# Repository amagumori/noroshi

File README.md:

# Noroshi
#### Portable LTE/Wifi Radio Terminal

Noroshi is a project that aims to explore the question:
**What capabilities enabled by the Internet are compelling, and...**
**How can we provide those capabilities in a way that is:**

+ More decentralized
+ More autonomous
+ More empowering for the individual?

The Internet of today is a vastly different place from the days of its infancy.  We've moved from a "many-servers" paradigm to a "many-clients" paradigm, as monolithic platforms have conquered the space.  The majority of Internet communication now exists in a TV-like paradigm, with a single-digit number of service providers.

These providers provide a variety of technological capabilities, each with unique social and cultural relevance, which overlap and can be broadly grouped into "live" and "static" groups, though the "liveness" is a spectrum.

### Live Capabilities
**Streaming** - Youtube, Twitch, IG Live, FB Live.
**Group Chat** - Discord, Slack, IRC (barely hanging on)
**Messaging** - Every platform

### Slow Capabilities
**Microblogging** - Twitter, IG, FB
**File Sharing** - Google Drive, Dropbox, OneDrive, etc
**Email** - Gmail, of course
**~~Blogging~~**  doesn't exist anymore
**~~Websites~~** don't exist anymore (in social or cultural relevance)

---

What would it look like to envision off-internet networking at a community or friend-group level?  And what capabilities could we provide while remaining free from the Internet or monolithic service providers?

The Internet provides a variety of capabilities, from realtime, streaming applications to static data.  We aim to attack this problem on both ends - one, the streaming, realtime, low-latency side of Internet functionality, using the NRF9160 to communicate over LTE; and the other, the slower, static side, using the ESP32 to enable peer-to-peer data exchange over Wifi.

### On the LTE side, a "radio" mode of using internet connectivity.  

+ Secure, frictionless, realtime push-to-talk communication, as with a VHF/UHF radio.

+ Broadcasting and receiving streaming audio, as with an FM radio.

Both of these applications are out of reach for the "regular citizen", especially within a city.  Ham radio does not enable encrypted communications, and is limited by regulation to a pure hobbyist pursuit.  Ham cannot be used for group-exclusive communications, and has a variety of limitations and frictions that prevent it from being a viable day-to-day communication tool.

On the other side, to set up a private VHF/UHF PTT capability within a city, a customer must lease radios from a vertically integrated provider, because only these will own repeater space on the local coverage points; you can get licensed, but a prohibitively expensive outlay is required to actually achieve full coverage in a metropolitan area.

These regulatory limitations prevent VHF/UHF from being used in an autonomous, secure, and self-sufficient manner.  Either you're a HAM, limited to communications-as-a-hobby - QSLs, etc; or you're a lessee of service from a provider.

This project aims to take a specific, compelling application of cell technology (low-latency audio streaming) and build a dedicated, stripped-down, and focused product for it, providing a more autonomous and open-source way to use IoT without relying on current monolithic tech ecosystems.

The goal of this project is to provide a different vision of communication over cell networks.  The value of this radio is in it being a dedicated object with a focused purpose and frictionless UX.  We aim for the main mode of interaction with the object to be physical, with the screen providing extremely concise information.  As far as possible from the interaction mode of a mobile app, we want this to be a physical device that fits well in the hand, has interactions recognizable by feel, and can be used without looking at the screen.

To illustrate this, mobile apps like Zello enable PTT functionality; but they also require buying into the entire cell phone ecosystem, from the hardware to the OS, and your communications go through an opaque signed binary to Zello's servers.  Cell phone apps have ever-present interaction friction at every level - multiple touch interactions to talk by default (unlocking the screen to hit the talk button, etc); coexisting with other apps on the phone, which can interfere with its operation or availability; difficulty of manipulating the phone in the hand; and so on.

Similarly, internet radio already exists; but there is no *dedicated* and simplified way to interact with it, and as such the technology is effectively dead.  Streaming video platforms such as Youtube or Twitch are now the dominant platform for audio streaming, because they provide lower barriers to entry and vastly better UX than Shoutcast or similar.  By providing a simple and frictionless way to broadcast and receive audio in realtime, we aim to empower individual users and rejuvenate a dying medium, with everyone being the owner, operator, and DJ of their own radio station, not through an app, but through a dedicated physical device.  Ultimately, I envision this as pushing a second age of radio, with individuals able to frictionlessly "speak" to an audience - every individual having space within the frequency spectrum, free of barriers to entry.

### Wifi / LoRa - Wifi for a peer-to-peer sneakernet, decoupled from the Internet.

The aim of the Wifi side of functionality is to provide a way to slowly and organically share static data among a local community without using the Internet - in other words, to provide a truly autonomous form of social networking.  

This aims at a similar area as existing platforms such as Mastodon that aim to provide decentralized alternatives to monolithic social networks. This project aims to provide a generic and open-ended framework for all types of information exchange - social applications like microblogging, as well as media and file sharing, forums, and wikis.  It also aims to provide a hardy and simple method for updating this shared state, that can be used not just with WiFi, but with other wireless connections - LoRa, etc.

## Design Methodology

We envision a community's "shared state" as a traditional filesystem, with each member possessing a directory.  At a global level, there are N numbers of dedicated *reserved filenames* that indicate the contextual meaning of the data.  a directory named "blog" will be viewed on the client side as that user's blog, similar to a twitter feed.  all files within that directory will be parsed as Markdown and displayed as blog entries in a time-sorted list based on the file's creation date.

### Connection

The public keys of "friends" in the community are indicated by the SSID broadcasted by the peer AP, and the shared secret is used as the WPA2 password.  With both devices in Station+SoftAP mode, operating in both modes simultaneously, we open a TCP socket connection.

### Syncing

After connecting to the peer, both clients send hashes of each "friend"'s directory, as well as timestamps of its last update.  both clients symmetrically use this info to determine the friends for which they own newer data, and the friends for which they own older data.

Another *reserved file* is the "friends" file.  This file exists within each person's directory at the top level, and describes permission groups (The ESP32 has a stripped-down libc, but runs on FreeRTOS, and has a very spare filesystem abstraction layer.)

We use **librsync**, specifically **rdiff**, to handle generating file signatures, deltas, and patching.  Signature files are generated AoT, not at connection time.

The friend directory trees are walked with **ftw**, permissions are checked, and the fds of new / updated signature files are pushed to a queue.  These signature files are compressed and sent; used to generate deltas; and deltas are compressed and sent, completing the sync process.

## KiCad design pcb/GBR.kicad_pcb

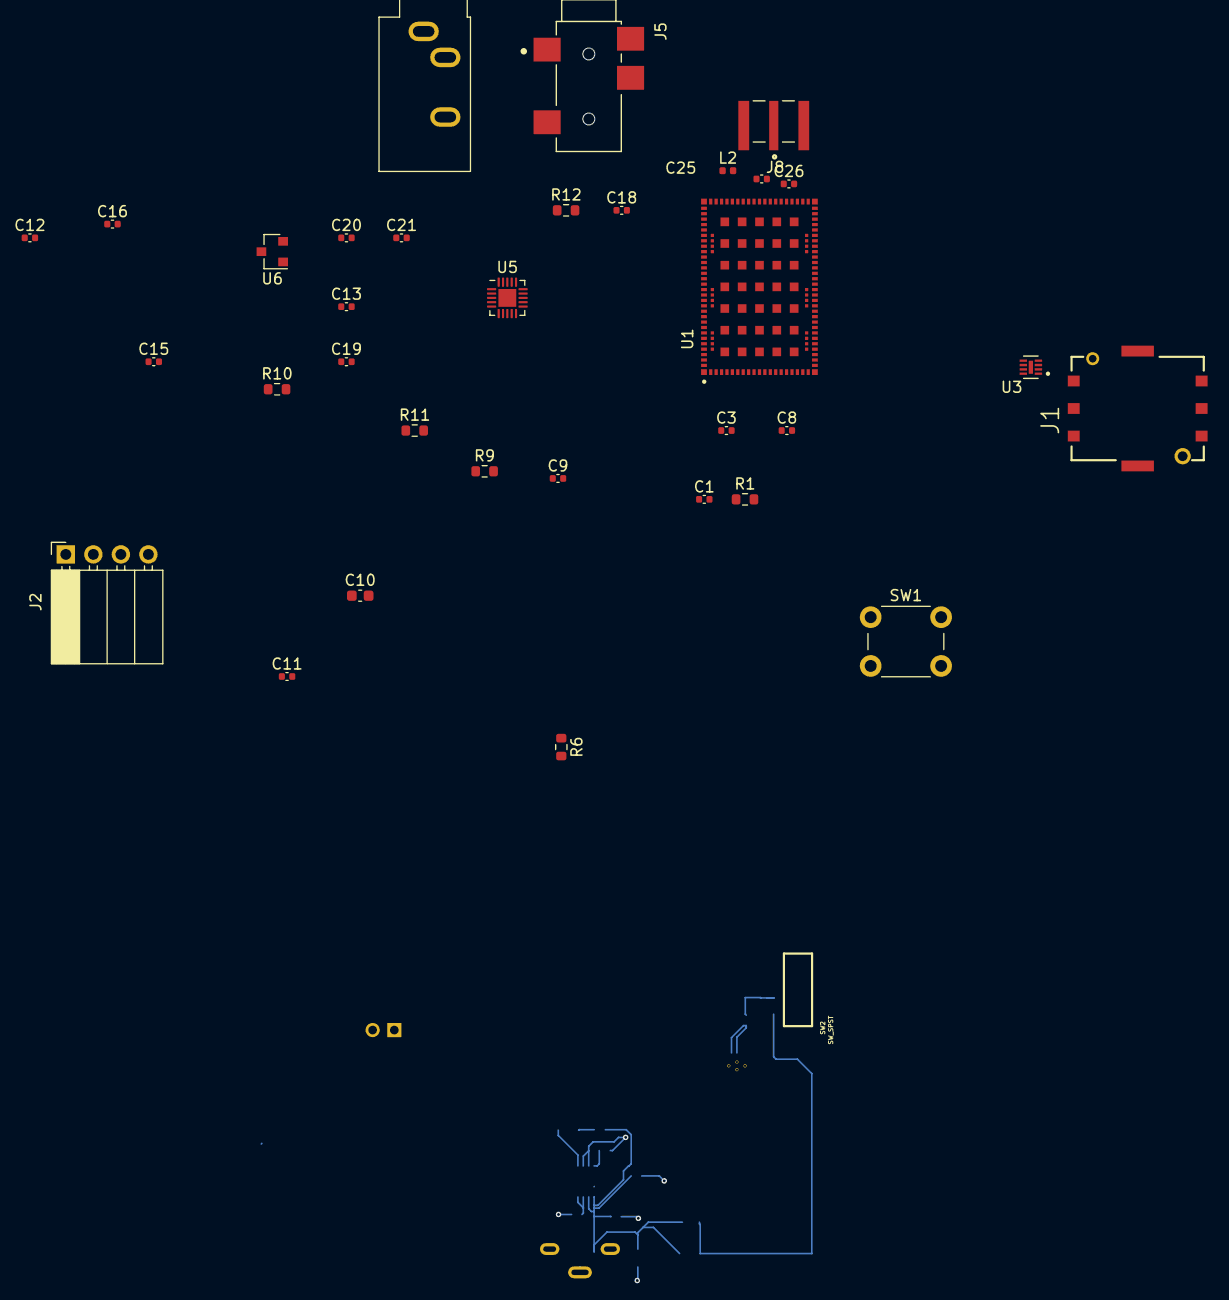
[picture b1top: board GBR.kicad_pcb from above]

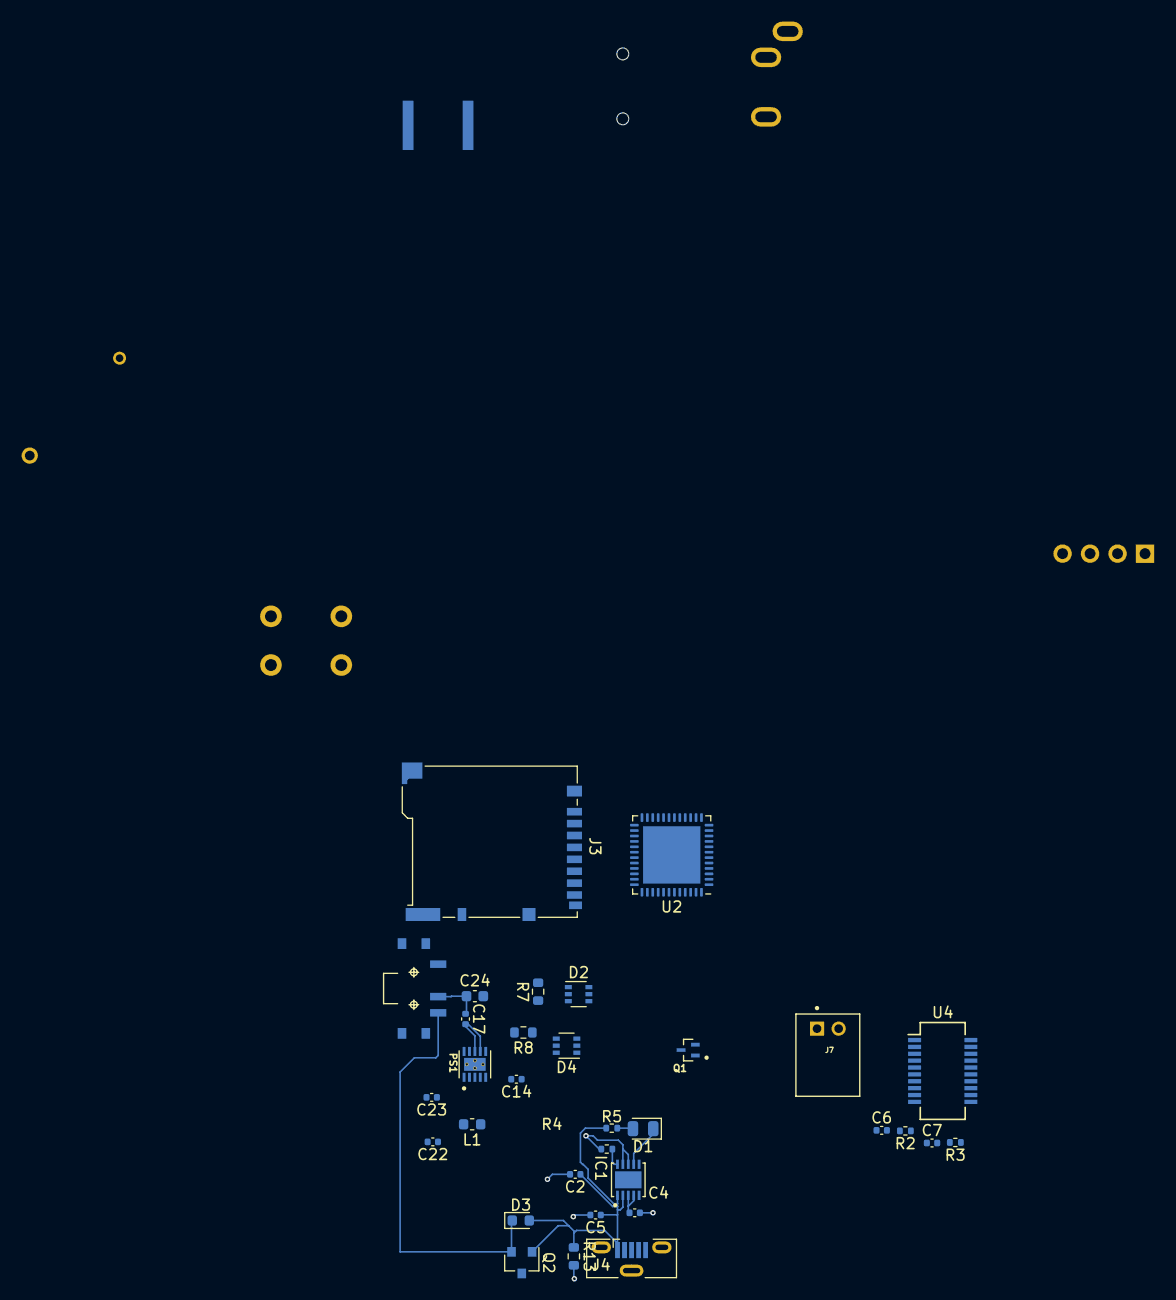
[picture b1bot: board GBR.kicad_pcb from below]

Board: 4 copper layers, 65 parts (32 on the bottom side), 59 nets.

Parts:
C1: 4.7uF; C_0402_1005Metric
C2: 1u; C_0402_1005Metric
C3, C8: 4.7u; C_0402_1005Metric
C4: C; C_0402_1005Metric
C5, C11, C13, C15, C18, C19: 0.1uF; C_0402_1005Metric
C6, C7: 47pF; C_0402_1005Metric
C9: 47u; C_0402_1005Metric
C10: C; C_0603_1608Metric
C12, C16, C20, C21: 1uF; C_0402_1005Metric
C14: 0.1u; C_0402_1005Metric
C17, C22, C23: 10u; C_0402_1005Metric
C24: 10uF; C_0603_1608Metric
C25, C26: 50V 15pF; C_0402_1005Metric
D1: LED; LED_0805_2012Metric
D2, D4: BAV70S; SOT-363_SC-70-6
D3: D_Schottky; D_0603_1608Metric
IC1: MCP73113-16SI_MF; SON50P300X300X100-11N(1)
J1: SIM8051-6-0-14-01-X-REVD; GCT_SIM8051-6-0-14-01-X-REVD
J2: ADAFRUIT OLED CONN; PinSocket_1x04_P2.54mm_Horizontal
J3: Micro_SD_Card; microSD_HC_Hirose_DM3BT-DSF-PEJS
J4: USB_B_Micro; USB_Micro-B_Molex-105133-0001
J5: headphones; CUI_SJ2-35863A1-SMT-TR
J6: line in; Jack_3.5mm_CUI_SJ1-3533NG_Horizontal
J7: Conn_01x02_Male; JST_S2B-PH-K-S(LF)(SN)
J8: LTE_ANT_SMA; TAOGLAS_EMPCB.SMAFSTJ.B.HT
L1: 1.5uH; L_0603_1608Metric
L2: 250mA 39nH; L_0402_1005Metric
PS1: TPS63031DSKR; SON50P250X250X80-11N
Q1: RE1C002UNTCL; SOTFL50P160X85-3N
Q2: DMG2301L; SOT-23
R1: 10K; R_0603_1608Metric
R2, R3: 27; R_0402_1005Metric
R4: R_PROG; R_0402_1005Metric
R5: R_US; R_0402_1005Metric
R6, R7, R9: 1M; R_0603_1608Metric
R8: 100k; R_0603_1608Metric
R10, R11: 4.7K; R_0603_1608Metric
R12: 2.2K; R_0603_1608Metric
R13: 100K; R_0603_1608Metric
SW1: SW_Push; SW_PUSH_6mm
SW2: SW_SPST; KPS-1290
U1: NRF9160-SICA-R7; XCVR_NRF9160-SICA-R7
U2: ESP32-PICO-D4; QFN-48-1EP_7x7mm_P0.5mm_EP5.3x5.3mm
U3: TPD3F303DQDR; SON40P170X135X80-9N
U4: FT231XS; SSOP-20_3.9x8.7mm_P0.635mm
U5: SGTL5000XNLA3; QFN-20-1EP_3x3mm_P0.4mm_EP1.65x1.65mm
U6: MCP1700-1202E_SOT23; SOT-23

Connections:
+1V8: C13.1, C16.1, U5.20, U6.2
+3V3: C3.1, C8.1, C11.1, C12.1, C15.1, C22.1, C23.1, PS1.1, PS1.10, R1.1, R9.1, R10.1, R11.1, U1.12, U1.22, U1.102, U2.1, U2.43, U2.46, U5.3, U5.12, U6.3
+BATT: C4.1, IC1.3, IC1.4, J7.2, Q2.3
-BATT: C1.2, C2.2, C3.2, C4.2, C5.2, C6.2, C7.2, C8.2, C9.2, C10.1, C11.2, C12.2, C13.2, C14.2, C15.2, C16.2, C19.2, C22.2, C23.2, C24.2, C25.2, IC1.8, IC1.9, J1.C5, J4.5, J4.6, J7.1, L2.2, PS1.3, PS1.9, PS1.11, Q1.2, R4.1, R6.1, R7.2, R13.2, U1.1, U1.5, U1.9, U1.14, U1.17, U1.21, U1.27, U1.31, U1.36, U1.41, U1.44, U1.47, U1.50, U1.52, U1.56, U1.60, U1.62, U1.63, U1.65, U1.66, U1.72, U1.74, U1.75, U1.76, U1.77, U1.78, U1.79, U1.80, U1.81, U1.82, U1.85, U1.90, U1.94, U1.98, U1.103_1, U1.103_2, U1.103_3, U1.103_4, U1.103_5, U1.103_6, U1.103_7, U1.103_8, U1.103_9, U1.103_10, U1.103_11, U1.103_12, U1.103_13, U1.103_14, U1.103_15, U1.103_16, U1.103_17, U1.103_18, U1.103_19, U1.103_20, U1.103_21, U1.103_22, U1.103_23, U1.103_24, U1.103_25, U1.103_26, U1.103_27, U1.103_28, U1.103_29, U1.103_30, U1.103_31, U1.103_32, U1.103_33, U1.103_34, U1.103_35, U2.49, U3.9, U4.3, U4.15, U5.21
/EN: Q1.1, R6.2
/SIM_CLK: U1.46, U3.7
/SIM_IO: U1.48, U3.6
/SIM_RST: U1.43, U3.8
/VIN: C17.1, C24.1
ESP_RESET: C1.1, R1.2, U2.9
LRCLK: U1.87, U5.14
LTE_ANT: C25.1, C26.2, U1.61
MCLK: U1.86, U5.13
MIC: C18.1, R12.1
MODE\2.2F: D2.4, D4.4
unnamed: C6.1, J4.2, R2.2
unnamed: C7.1, J4.3, R3.2
unnamed: C9.1, U1.13
unnamed: C10.2, U4.16
unnamed: C14.1, C17.2, PS1.5, PS1.7, PS1.8
unnamed: C18.2, U5.10
unnamed: C19.1, U5.5
unnamed: C20.2, U5.8
unnamed: C21.1, J6.T
unnamed: C21.2, U5.9
unnamed: C26.1, J8.1, L2.1
unnamed: D1.1, IC1.7
unnamed: D1.2, R5.1
unnamed: D2.3, R7.1, R8.2
unnamed: D3.1, Q2.2
unnamed: IC1.10, R4.2
unnamed: J1.C2, U3.1
unnamed: J1.C3, U3.2
unnamed: J1.C7, U3.3
unnamed: J3.2, U2.11
unnamed: J3.3, U2.30
unnamed: J3.4, U2.26
unnamed: J3.5, U2.31
unnamed: J3.7, U2.32
unnamed: J3.8, U2.33
unnamed: L1.1, PS1.4
unnamed: L1.2, PS1.2
unnamed: PS1.6, Q1.3, R8.1
unnamed: R9.2, U1.101
unnamed: R10.2, U5.19
unnamed: R11.2, U5.18
unnamed: R12.2, U5.11
unnamed: U1.6, U1.7, U1.8, U1.10, U1.11, U1.51, U1.68, U1.69, U1.70, U1.71, U1.73, U1.104, U1.105, U1.106, U1.107, U1.108, U1.109, U1.110, U1.111, U1.112, U1.113, U1.114, U1.115, U1.116, U1.117, U1.118, U1.119, U1.120, U1.121, U1.122, U1.123, U1.124, U1.125, U1.126, U1.127
unnamed: U2.3, U2.4
OLED_MISO: J2.3, U1.96
OLED_MOSI: J2.2, U1.97
OLED_SCK: J2.4, U1.95
P0.31\NRF_PS_EN\1.1B: D2.1, U1.89
RTC_PS_EN\3.6C: D2.5, D4.5
SCLK: U1.30, U5.15
SDIN: U1.84, U5.17
SDOUT: U1.83, U5.16
SIM_VCC: J1.C1, U1.49, U3.5
VBUS: C2.1, C5.1, D2.2, D3.2, IC1.1, IC1.2, J4.1, Q2.1, R5.2, R13.1, U4.6

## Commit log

2021-11-27 firmware thoughts
2022-01-04 building lwm2m client
2022-01-09 pdm mic device interface
2022-01-10 implementing lwm2m client and interchange objects.
2022-01-10 mic and radio changes.
2022-01-10 changing cmakefiles setup
2022-01-22 implementing MQTT
2022-01-25 speaker side of codec
2022-01-28 designing the world's dumbest voip protocol
2022-01-28 hammering out voip
2022-01-28 cleanup
2022-01-30 refactoring modem and radio
2022-02-01 connecting I2S and Radio modules.
2022-02-01 first draft of I2S / Codec2 interface
2022-02-02 began implementing UART interface.
2022-02-06 adding module threads and other stuff.
2022-02-24 adding ESP32 firmware
2022-03-08 integrating librsync
2022-03-08 remove tagfile
2022-03-14 implementing sync with rdiff, ftw, esp-now
2022-03-21 working at rdiff syncing on ESP32 side, implemented UART interface for sending ESP32 state to NRF9160.
2022-03-22 added description of the project goals and methodology to the README.
2022-04-08 ESP32: rsync, exchanging file info over socket before generating signatures.
2022-05-04 opus audio codec
2022-05-04 wrapping up audio system
2022-05-08 MQTT refactoring; added libopus dependencies
2022-05-28 adding support for outputting multiple audio streams at once
2022-06-03 event stuff
2022-06-23 adding kicad project and PCB stuff.
2022-07-09 miscellaneous progress...bad commit message
2022-07-09 removed ctags file, whoops
2022-07-16 esp32 stuff
2022-07-17 beginning to tie the ESP32 side together.
2022-07-18 reorganize
2022-07-19 elliptic curve diffie key exchange with ESP-NOW.
